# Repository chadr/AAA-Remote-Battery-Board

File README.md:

# AAA Remote Battery Board - Updated!
 Remote RTC/CMOS/NVRAM battery for retro computer motherboards. Provides about +4.5V. Which is what most vintage motherboards require. +3V, like from a CR2032, is not appropriate!

 **Features:**
 * Higher voltage than CR2032 and higher capacity for longer life
 * Diode to prevent reverse charging
 * Diode delete solder jumper - NEW
 * Universal fuse holder footprint accepts wide and narrow spacing - NEW
 * 100ma fuse to protect motherboard if a short develops
 * Nylon fuse holder contains fuse blast and glass
 * Uses 1x4 pin headers found on most motherboards for simple cabling
 * PCB cutouts for Cable tie to secure batteries in rough service situations
 * Backer board to raise battery off case when using tape/velcro - NEW
 * Mounting holes for M3 standoffs
 * No motherboard modifications required!

<picture>
 
</picture>

<picture>
  
</picture>

<picture>
 
</picture>

## Here's a scan from a 386sx AT motherboard. Notice the voltages it requires. It warns against using +3V batteries like a CR2032!
<picture>
  
</picture>

## Bill of Materials
**Item**|**Qty**|**MFG Part Num**|**Mouser Part Num**
:-----:|:-----:|:-----:|:-----:
Keystone 3xAAA Holder|1|2479|534-2479
1N4148 Diode|1|1N4148-T50R|512-1N4148T50R
1x4 2.54mm Male Header|1|826926-4|571-826926-4
Fuse|1|BK1/GMC-100-R|504-BK1-GMC-100-R
Fuse Holder|1|0PTF0078P|576-0PTF0078P
Fuse Clip|1|00BS0232P|576-00BS0232P

## Board Information
Dimensions:  
Layers: 2  
Finish: HASL  
Make sure to choose "custom position" for order number /w JLCPCB or PCBWAY.  

## Purchasing
I sell assembled kits complete with cables, mounting hardware, and batteries in my [eBay store](https://www.ebay.com/str/pcrestoration).  
And on Tindie (Cheaper on Tindie due to lower fees!) [Link](https://www.tindie.com/products/33599/)

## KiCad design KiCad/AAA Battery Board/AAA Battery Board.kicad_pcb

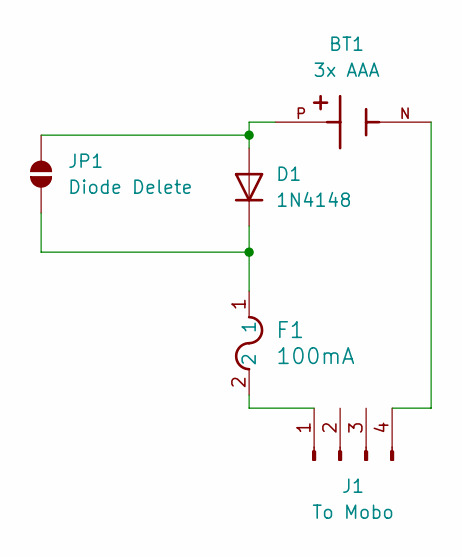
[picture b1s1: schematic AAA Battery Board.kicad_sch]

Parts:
BT1: 3x AAA; BAT_2479; PARTREV E
D1: 1N4148; D_DO-35_SOD27_P7.62mm_Horizontal
F1: 100mA; UniversalGreenFuseHolder
J1: To Mobo; PinHeader_1x04_P2.54mm_Vertical
JP1: Diode Delete; SolderJumper-2_P1.3mm_Open_TrianglePad1.0x1.5mm

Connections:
unnamed: BT1.P, D1.2 (A), JP1.1 (A)
unnamed: D1.1 (K), F1.1, JP1.2 (B)
unnamed: F1.2, J1.1
unnamed: BT1.N, J1.4

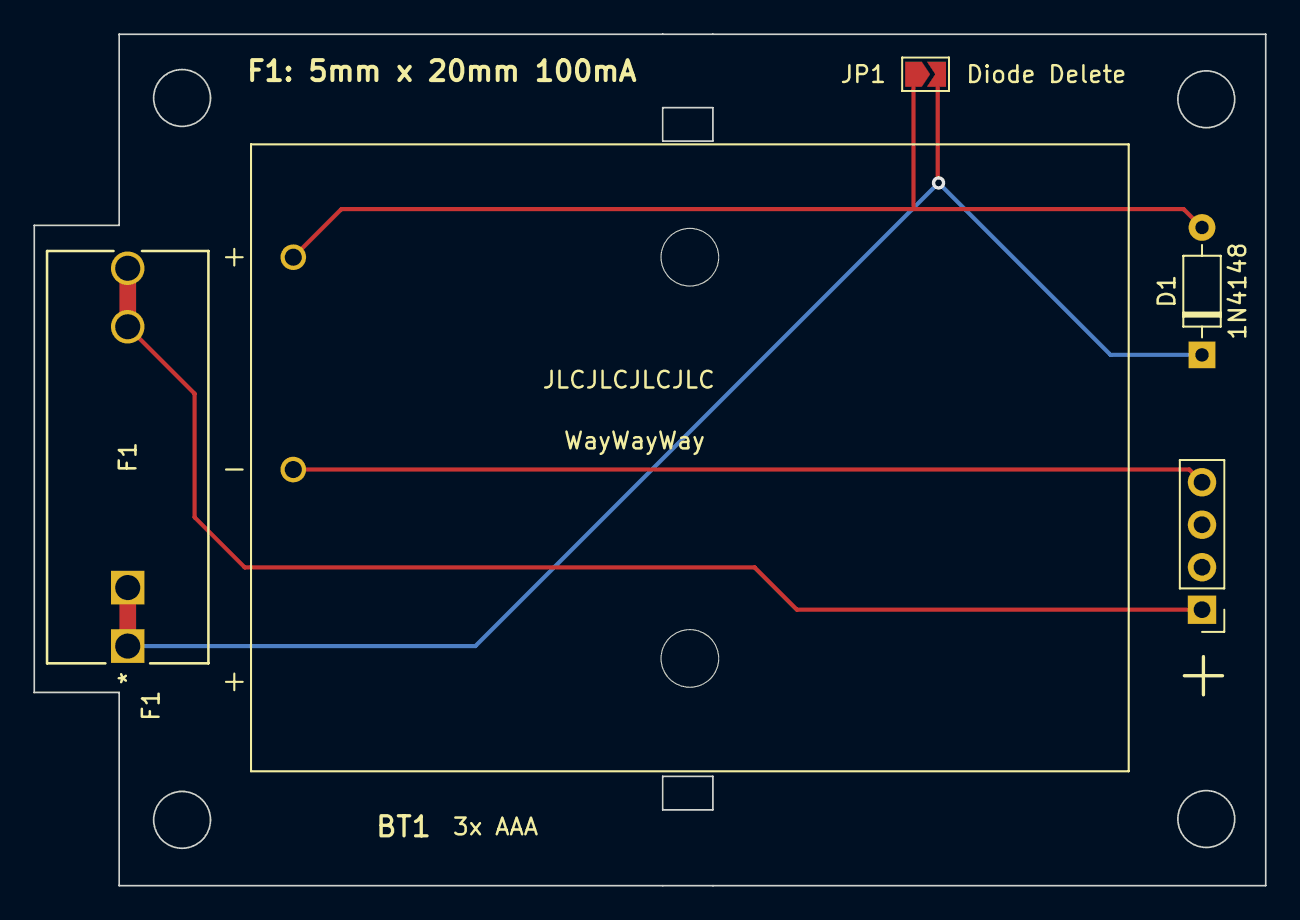
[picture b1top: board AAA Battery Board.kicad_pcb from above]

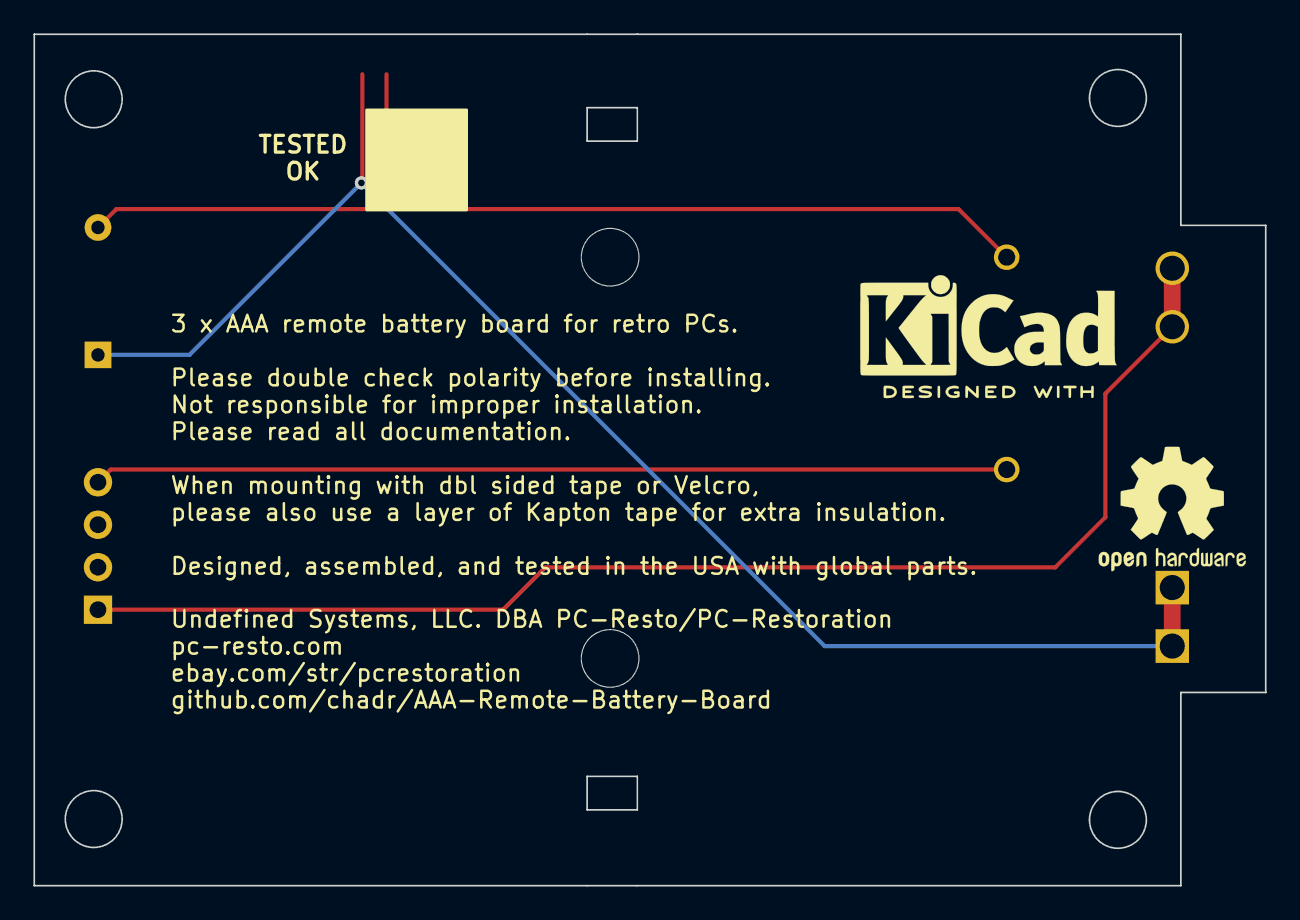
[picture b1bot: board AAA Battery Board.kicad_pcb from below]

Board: 2 copper layers, 73.7 x 50.9 mm, 7 parts (2 on the bottom side), 4 nets.

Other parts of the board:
KiCad Logo: KiCad-Logo2_6mm_SilkScreen
Open Hardware Logo: OSHW-Logo2_9.8x8mm_SilkScreen

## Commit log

2023-11-16 update files
2023-11-27 Add zip tie holes
2023-12-19 update PCB
    add cutouts for zip ties
2024-01-19 add images
2024-01-20 fix typos
2024-02-02 add docs
2024-07-28 update images and filenames
2024-12-05 Update footprints.
    Update fuse holder footprint to work with both 15mm and 23mm leg spacing versions.
2025-02-24 update design + files
